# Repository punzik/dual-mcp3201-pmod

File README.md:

# Модуль PMOD с двумя АЦП MCP3201

На модуле установлены два АЦП __MCP3201__ (интерфейс SPI), источник опорного
напряжения __REF3030__ с напряжением 3.0В и антиалиасинговые фильтры с полосой
10Гц-10кГц. Распиновка разъема PMOD стандартная:

| Pin | Signal | Dir. |
|-----|--------|------|
| 1   | SS_N_L | IN   |
| 2   | --     |      |
| 3   | MISO_L | OUT  |
| 4   | SCLK_L | IN   |
| 5   | GND    |      |
| 6   | +3.3V  |      |
| 7   | SS_N_R | IN   |
| 8   | --     |      |
| 9   | MISO_R | OUT  |
| 10  | SCLK_R | IN   |
| 11  | GND    |      |
| 12  | +3.3V  |      |

3D рендер платы:

АЧХ антиалиасинговых фильтров:

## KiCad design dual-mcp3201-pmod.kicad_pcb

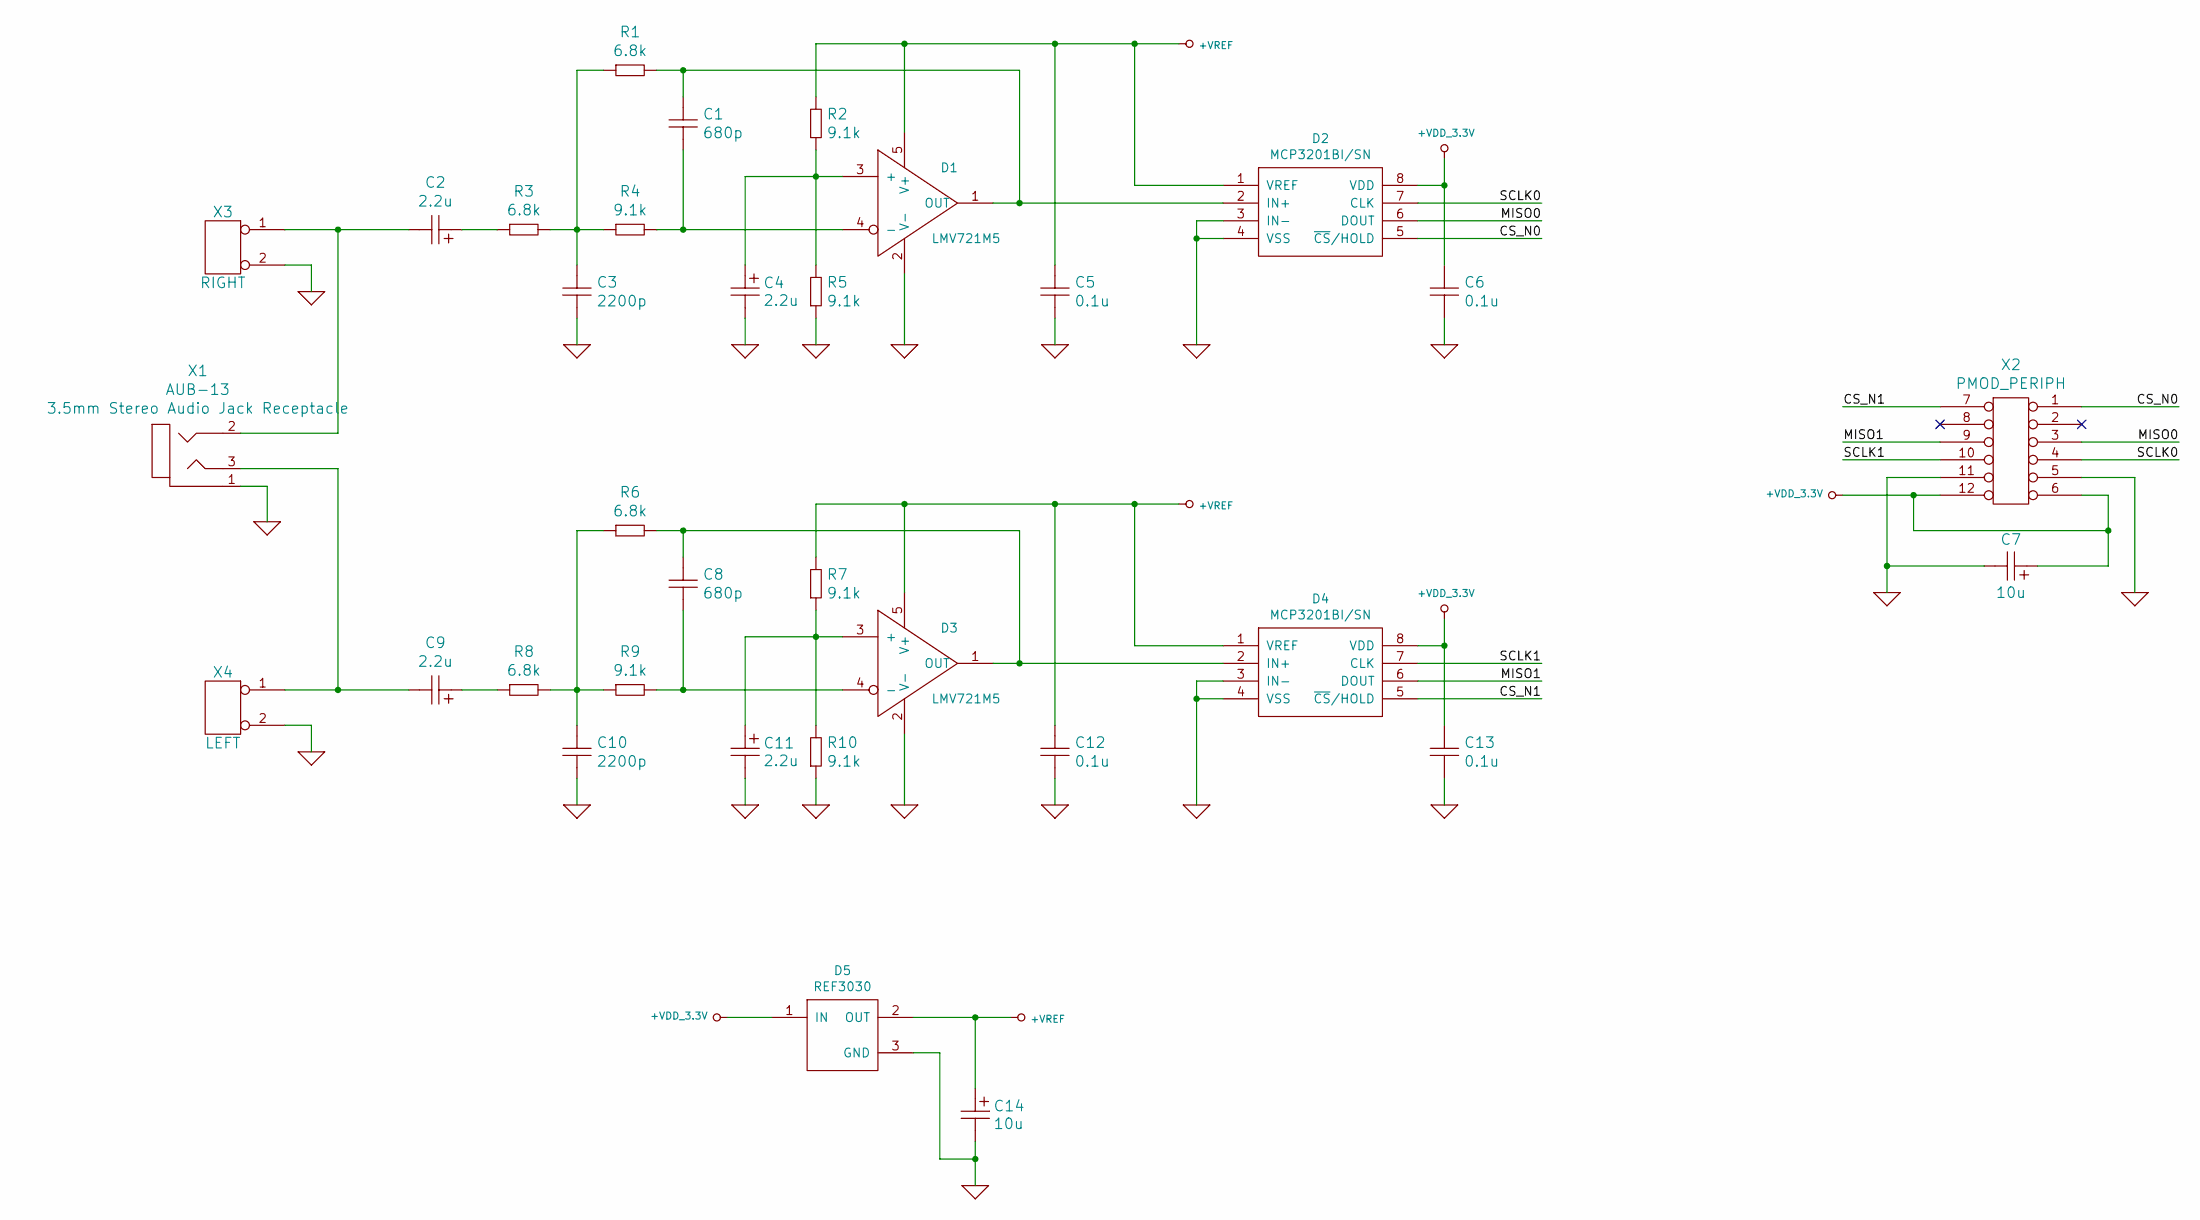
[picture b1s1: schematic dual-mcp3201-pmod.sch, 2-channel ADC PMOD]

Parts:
C1, C8: 680p; C_0603_1608Metric_Pad1.05x0.95mm_HandSolder; Voltage 50V
C2, C4, C9, C11: 2.2u; CP_EIA-3216-18_Kemet-A_Pad1.58x1.35mm_HandSolder; Voltage 10V; PartNumber 293D225X9010A2TE3
C3, C10: 2200p; C_0603_1608Metric_Pad1.05x0.95mm_HandSolder; Voltage 50V
C5, C6, C12, C13: 0.1u; C_0603_1608Metric_Pad1.05x0.95mm_HandSolder; Voltage 16V
C7, C14: 10u; CP_EIA-3216-18_Kemet-A_Pad1.58x1.35mm_HandSolder; Voltage 10V; PartNumber 293D106X9010A2TE3
D1, D3: LMV721M5; SOT-23-5_HandSoldering; PartNumber LMV721M5
D2, D4: MCP3201BI/SN; SOP-8_3.76x4.96mm_P1.27mm; PartNumber MCP3201BI/SN
D5: REF3030; SOT-23_Handsoldering; PartNumber REF3030
R1, R3, R6, R8: 6.8k; C_0603_1608Metric_Pad1.05x0.95mm_HandSolder; Tolerance 1%
R2, R4, R5, R7, R9, R10: 9.1k; C_0603_1608Metric_Pad1.05x0.95mm_HandSolder; Tolerance 1%
X1: AUB-13; JACK_ST_AUB_13; PartNumber AUB-13
X2: PMOD_PERIPH; PartNumber PLD-12R (PLD-80R)
X3: RIGHT; PinHeader_1x02_P2.54mm_Vertical; PartNumber PLS-2 (PLS-40)
X4: LEFT; PinHeader_1x02_P2.54mm_Vertical; PartNumber PLS-2 (PLS-40)

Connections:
+VDD_3.3V: C6.2, C7.1, C13.2, D2.8 (VDD), D4.8 (VDD), D5.1 (IN), X2.6, X2.12
+VREF: C5.2, C12.2, C14.1, D1.5 (V+), D2.1 (VREF), D3.5 (V+), D4.1 (VREF), D5.2 (OUT), R2.2, R7.2
/CS_N0: D2.5 (~CS~/HOLD), X2.1
/CS_N1: D4.5 (~CS~/HOLD), X2.7
/MISO0: D2.6 (DOUT), X2.3
/MISO1: D4.6 (DOUT), X2.9
/SCLK0: D2.7 (CLK), X2.4
/SCLK1: D4.7 (CLK), X2.10
GND: C3.1, C4.2, C5.1, C6.1, C7.2, C10.1, C11.2, C12.1, C13.1, C14.2, D1.2 (V-), D2.3 (IN-), D2.4 (VSS), D3.2 (V-), D4.3 (IN-), D4.4 (VSS), D5.3 (GND), R5.1, R10.1, X1.1, X2.5, X2.11, X3.2 (PM), X4.2 (PM)
unnamed: C1.1, D1.4 (-), R4.2
unnamed: C1.2, D1.1 (OUT), D2.2 (IN+), R1.2
unnamed: C2.1, R3.1
unnamed: C2.2, X1.2, X3.1
unnamed: C3.2, R1.1, R3.2, R4.1
unnamed: C4.1, D1.3 (+), R2.1, R5.2
unnamed: C8.1, D3.4 (-), R9.2
unnamed: C8.2, D3.1 (OUT), D4.2 (IN+), R6.2
unnamed: C9.1, R8.1
unnamed: C9.2, X1.3, X4.1
unnamed: C10.2, R6.1, R8.2, R9.1
unnamed: C11.1, D3.3 (+), R7.1, R10.2

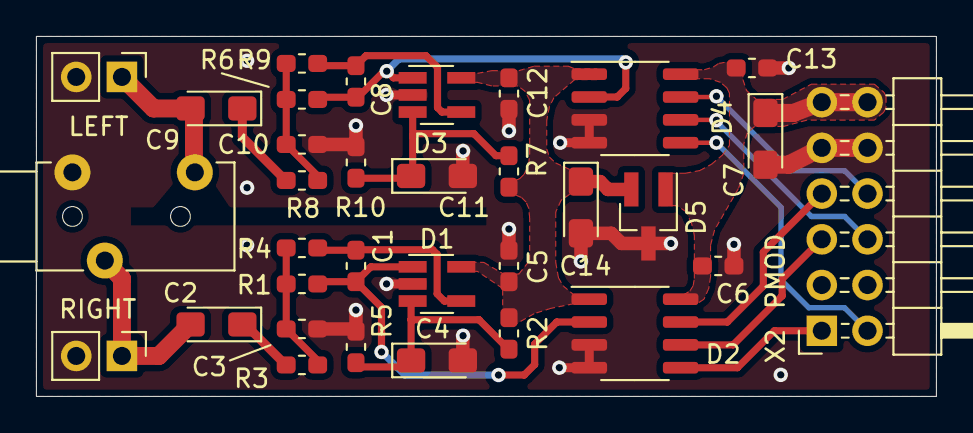
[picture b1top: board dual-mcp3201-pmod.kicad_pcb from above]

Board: 2 copper layers, 50.0 x 20.0 mm, 33 parts (0 on the bottom side), 21 nets.

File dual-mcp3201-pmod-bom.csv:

Reference, Quantity, Value, Footprint, Datasheet, Description, Package, PartNumber, Spice_Lib_File, Spice_Model, Spice_Netlist_Enabled, Spice_Node_Sequence, Spice_Primitive, Tolerance, Type, Voltage
C1 C8 ,2,"680p","Capacitor_SMD:C_0603_1608Metric_Pad1.05x0.95mm_HandSolder","","SMD Ceramic Capacitor NP0","0603","-","","","","","","-","NP0","50V"
C7 C14 ,2,"10u","Capacitor_Tantalum_SMD:CP_EIA-3216-18_Kemet-A_Pad1.58x1.35mm_HandSolder","","SMD Tantalum Capacitor","A-CASE","293D106X9010A2TE3","","","","","","-","Tantalum","10V"
C2 C4 C9 C11 ,4,"2.2u","Capacitor_Tantalum_SMD:CP_EIA-3216-18_Kemet-A_Pad1.58x1.35mm_HandSolder","","SMD Tantalum Capacitor","A-CASE","293D225X9010A2TE3","","","","","","-","Tantalum","10V"
C3 C10 ,2,"2200p","Capacitor_SMD:C_0603_1608Metric_Pad1.05x0.95mm_HandSolder","","SMD Ceramic Capacitor NP0","0603","-","","","","","","-","NP0","50V"
C5 C6 C12 C13 ,4,"0.1u","Capacitor_SMD:C_0603_1608Metric_Pad1.05x0.95mm_HandSolder","","SMD Ceramic Capacitor X7R","0603","-","","","","","","-","X7R","16V"
D1 D3 ,2,"LMV721M5","Package_TO_SOT_SMD:SOT-23-5_HandSoldering","","OpAMP","SOT-23-5","LMV721M5","spice/lmv721.lib","lmv721","Y","3 4 1 5 2","X","","",""
D2 D4 ,2,"MCP3201BI/SN","Package_SO:SOP-8_3.76x4.96mm_P1.27mm","","ADC","SO-8-150","MCP3201BI/SN","","","","","","","",""
D5 ,1,"REF3030","Package_TO_SOT_SMD:SOT-23_Handsoldering","","LDO Reference Voltage Source","SOT-23-3","REF3030","","","","","","","",""
R1 R3 R6 R8 ,4,"6.8k","Capacitor_SMD:C_0603_1608Metric_Pad1.05x0.95mm_HandSolder","","SMD Resistor","0603","-","","","","","","1%","",""
R2 R4 R5 R7 R9 R10 ,6,"9.1k","Capacitor_SMD:C_0603_1608Metric_Pad1.05x0.95mm_HandSolder","","SMD Resistor","0603","-","","","","","","1%","",""
X1 ,1,"AUB-13","local:JACK_ST_AUB_13","","3.5mm Stereo Audio Jack Receptacle","","AUB-13","","","","","","","",""
X2 ,1,"PMOD_PERIPH","local:PMOD_PERIPH","","Right-angle 2.54mm pin-header","","PLD-12R (PLD-80R)","","","","","","","",""
X3 ,1,"RIGHT","Connector_PinHeader_2.54mm:PinHeader_1x02_P2.54mm_Vertical","","2.54mm 2-pin connector","","PLS-2 (PLS-40)","","","","","","","",""
X4 ,1,"LEFT","Connector_PinHeader_2.54mm:PinHeader_1x02_P2.54mm_Vertical","","2.54mm 2-pin connector","","PLS-2 (PLS-40)","","","","","","","",""

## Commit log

2021-01-25 Initial commit. First release
2021-01-25 Fix README
2021-01-25 Add TAPR Open Hardware License file
2021-01-26 Connect flying via to ground
2021-01-29 Change filter cut-off frequency to 10kHz
2021-01-29 Update BOM
2021-02-16 Fix and update manufacturing files
